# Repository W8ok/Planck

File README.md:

## Planck - My tiny programmable blinking LED circuit

My autism decided to get into homebrew computing, but i didnt know where to start with actual circuits.  
So I decided to go as simple as possible while keeping it pretty.  
This idea lead to this project and its future comings.  
The plan was to make a series of projects to slowly expand on making small "computer" systems with simple building blocks.  
For this first project those building blocks was just discrete components.  

The circuit is made from a simple clock running at about 1Hz feeding into two D-Flipflops acting as a 2-bit counter.  
This 2-bit output is fed into a multiplexer circuit which then provides power to the corresponding 4-bit diode-matrix ROM.  
The ROM is programmed by inserting diodes in specific positions to create the desired LED blink pattern.  
All in all, a splendid little passion project of mine.  

# Goals
Make a simple system using discrete components to program an LED blink sequence.  
Build it up on a PCB of some kind to hang on my wall for pretty kinetic art.  

# Status
Circuit - Finished  
PCB - Finished example (May make a better one eventually)  
Physical build - No (Only done on breadboard during design phase)  

# Schematic

# Components
It is possible i miscounted, but im pretty sure i got it right  
|**Component**|**Value**|**Quantity**|**Notes**|
|:---|:---|:---|:---|
|**Resistors**|`220`|4||
||`1k`|2||
||`4.7k`|1||
||`10k`|22||
||`100k`|12||
||`1M`|2||
|**Capacitors**|`10n`|4||
||`4.7u`|2|I used polarized but not strictly needed|
|**Transistors**|`NPN`|23|2n2222 worked just fine|
|**Diodes**|`Diode`|4+16|16 for the diode ROM|
||`LED`|6|I used 2 green for address and 4 red for output|
|**Connectors**|`2x4`|4|This is where the diodes are used to program the ROM|

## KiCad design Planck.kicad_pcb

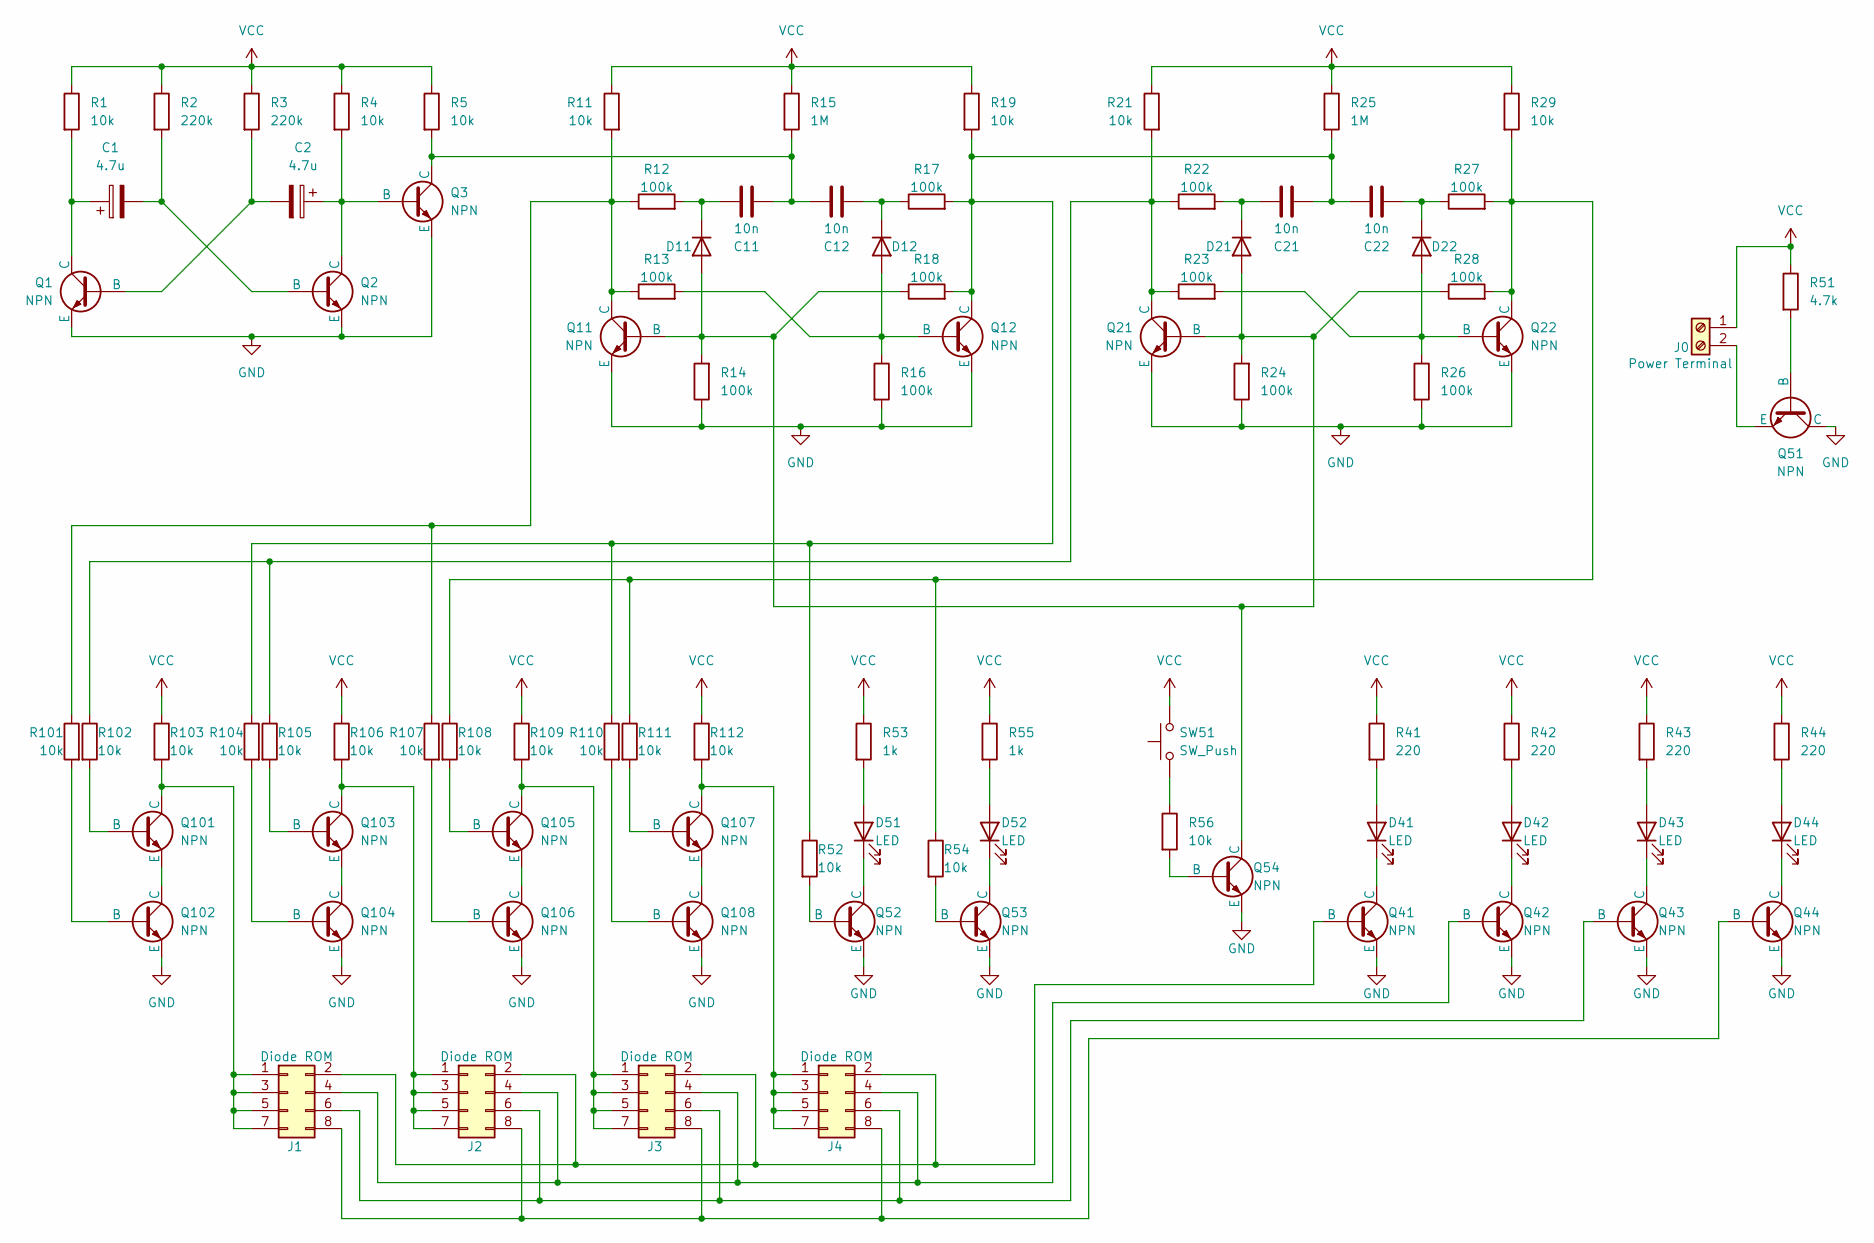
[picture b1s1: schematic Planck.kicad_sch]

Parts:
C1, C2: 4.7u; CP_Radial_D5.0mm_P2.50mm
C11, C12, C21, C22: 10n; C_Disc_D3.0mm_W2.0mm_P2.50mm
D11, D12, D21, D22: D; D_DO-34_SOD68_P7.62mm_Horizontal
D41, D42, D43, D44, D51, D52: LED; LED_D5.0mm
J0: Power Terminal; TerminalBlock_MaiXu_MX126-5.0-02P_1x02_P5.00mm
J1, J2, J3, J4: Diode ROM; PinHeader_2x04_P2.54mm_Vertical
Q1, Q2, Q3, Q11, Q12, Q21, Q22, Q41, Q42, Q43, Q44, Q51, Q52, Q53, Q54, Q101, Q102, Q103, Q104, Q105, Q106, Q107, Q108: NPN; TO-92
R1, R4, R5, R11, R19, R21, R29, R52, R54, R56, R101, R102, R103, R104, R105, R106, R107, R108, R109, R110, R111, R112: 10k; R_Axial_DIN0204_L3.6mm_D1.6mm_P5.08mm_Horizontal
R2, R3: 220k; R_Axial_DIN0204_L3.6mm_D1.6mm_P5.08mm_Horizontal
R12, R13, R14, R16, R17, R18, R22, R23, R24, R26, R27, R28: 100k; R_Axial_DIN0204_L3.6mm_D1.6mm_P5.08mm_Horizontal
R15, R25: 1M; R_Axial_DIN0204_L3.6mm_D1.6mm_P5.08mm_Horizontal
R41, R42, R43, R44: 220; R_Axial_DIN0204_L3.6mm_D1.6mm_P5.08mm_Horizontal
R51: 4.7k; R_Axial_DIN0204_L3.6mm_D1.6mm_P5.08mm_Horizontal
R53, R55: 1k; R_Axial_DIN0204_L3.6mm_D1.6mm_P5.08mm_Horizontal
SW51: SW_Push; SW_PUSH_6mm

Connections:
GND: Q1.3 (E), Q2.3 (E), Q3.3 (E), Q11.3 (E), Q12.3 (E), Q21.3 (E), Q22.3 (E), Q41.3 (E), Q42.3 (E), Q43.3 (E), Q44.3 (E), Q51.1 (C), Q52.3 (E), Q53.3 (E), Q54.3 (E), Q102.3 (E), Q104.3 (E), Q106.3 (E), Q108.3 (E), R14.1, R16.2, R24.1, R26.2
unnamed: D11.2 (A), D21.2 (A), Q11.2 (B), Q21.2 (B), Q54.1 (C), R14.2, R18.1, R24.2, R28.1
unnamed: C11.1, D11.1 (K), R12.2
unnamed: D12.2 (A), Q12.2 (B), R13.2, R16.1
unnamed: C12.2, D12.1 (K), R17.1
unnamed: C21.1, D21.1 (K), R22.2
unnamed: D22.2 (A), Q22.2 (B), R23.2, R26.1
unnamed: C22.2, D22.1 (K), R27.1
unnamed: D41.2 (A), R41.2
unnamed: D41.1 (K), Q41.1 (C)
unnamed: D42.2 (A), R42.2
unnamed: D42.1 (K), Q42.1 (C)
unnamed: D43.2 (A), R43.2
unnamed: D43.1 (K), Q43.1 (C)
unnamed: D44.2 (A), R44.2
unnamed: D44.1 (K), Q44.1 (C)
unnamed: D51.2 (A), R53.2
unnamed: D51.1 (K), Q52.1 (C)
unnamed: D52.2 (A), R55.2
unnamed: D52.1 (K), Q53.1 (C)
unnamed: J0.2, Q51.3 (E)
unnamed: J1.1, J1.3, J1.5, J1.7, Q101.1 (C), R103.2
unnamed: J1.2, J2.2, J3.2, J4.2, Q41.2 (B)
unnamed: J1.4, J2.4, J3.4, J4.4, Q42.2 (B)
unnamed: J1.6, J2.6, J3.6, J4.6, Q43.2 (B)
unnamed: J1.8, J2.8, J3.8, J4.8, Q44.2 (B)
unnamed: J2.1, J2.3, J2.5, J2.7, Q103.1 (C), R106.2
unnamed: J3.1, J3.3, J3.5, J3.7, Q105.1 (C), R109.2
unnamed: J4.1, J4.3, J4.5, J4.7, Q107.1 (C), R112.2
unnamed: C2.2, Q1.2 (B), R3.2
unnamed: C1.1, Q1.1 (C), R1.2
unnamed: C1.2, Q2.2 (B), R2.2
unnamed: C2.1, Q2.1 (C), Q3.2 (B), R4.2
unnamed: C11.2, C12.1, Q3.1 (C), R5.2, R15.2
unnamed: Q11.1 (C), R11.2, R12.1, R13.1, R101.1, R107.1
unnamed: C21.2, C22.1, Q12.1 (C), R17.2, R18.2, R19.2, R25.2, R52.1, R104.1, R110.1
unnamed: Q21.1 (C), R21.2, R22.1, R23.1, R102.1, R105.1
unnamed: Q22.1 (C), R27.2, R28.2, R29.2, R54.1, R108.1, R111.1
unnamed: Q51.2 (B), R51.2
unnamed: Q52.2 (B), R52.2
unnamed: Q53.2 (B), R54.2
unnamed: Q54.2 (B), R56.2
unnamed: Q101.2 (B), R102.2
unnamed: Q101.3 (E), Q102.1 (C)
unnamed: Q102.2 (B), R101.2
unnamed: Q103.2 (B), R105.2
unnamed: Q103.3 (E), Q104.1 (C)
unnamed: Q104.2 (B), R104.2
unnamed: Q105.2 (B), R108.2
unnamed: Q105.3 (E), Q106.1 (C)
unnamed: Q106.2 (B), R107.2
unnamed: Q107.2 (B), R111.2
unnamed: Q107.3 (E), Q108.1 (C)
unnamed: Q108.2 (B), R110.2
unnamed: R56.1, SW51.1
VCC: J0.1, R1.1, R2.1, R3.1, R4.1, R5.1, R11.1, R15.1, R19.1, R21.1, R25.1, R29.1, R41.1, R42.1, R43.1, R44.1, R51.1, R53.1, R55.1, R103.1, R106.1, R109.1, R112.1, SW51.2

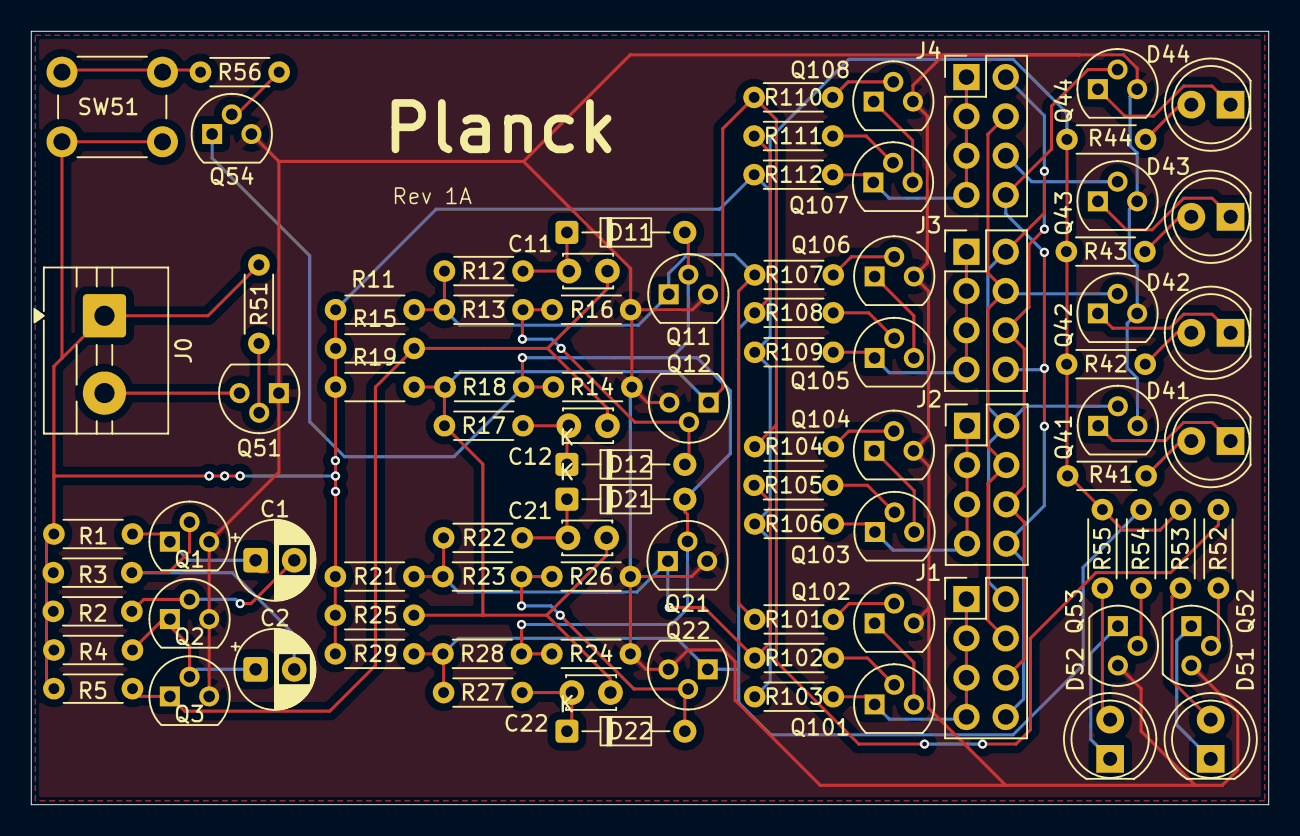
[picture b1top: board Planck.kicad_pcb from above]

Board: 2 copper layers, 80.0 x 50.0 mm, 90 parts (0 on the bottom side), 56 nets.

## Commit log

2026-01-01 Finalized First commit
2026-01-01 Fixed the .gitignore to ignore backups
2026-01-03 Fixed the .gitignore to ignore zipfiles to prevent backups from being added
